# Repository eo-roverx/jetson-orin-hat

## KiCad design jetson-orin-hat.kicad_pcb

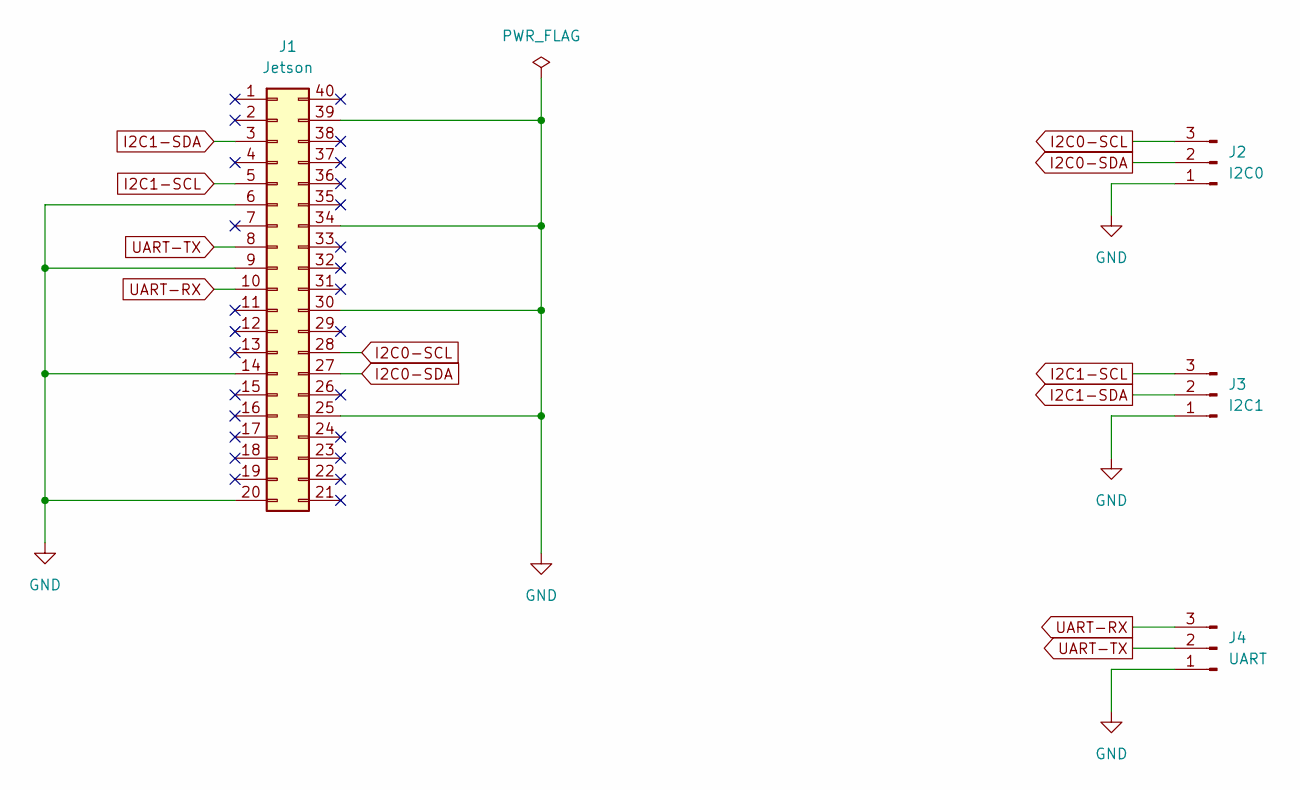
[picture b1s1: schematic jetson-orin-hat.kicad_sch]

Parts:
J1: Jetson; PinHeader_2x20_P2.54mm_Vertical
J2: I2C0; JST_PH_B3B-PH-K_1x03_P2.00mm_Vertical
J3: I2C1; JST_PH_B3B-PH-K_1x03_P2.00mm_Vertical
J4: UART; JST_PH_B3B-PH-K_1x03_P2.00mm_Vertical

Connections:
GND: J1.6, J1.9, J1.14, J1.20, J1.25, J1.30, J1.34, J1.39, J2.1, J3.1, J4.1
I2C0-SCL: J1.28, J2.3
I2C0-SDA: J1.27, J2.2
I2C1-SCL: J1.5, J3.3
I2C1-SDA: J1.3, J3.2
UART-RX: J1.10, J4.3
UART-TX: J1.8, J4.2

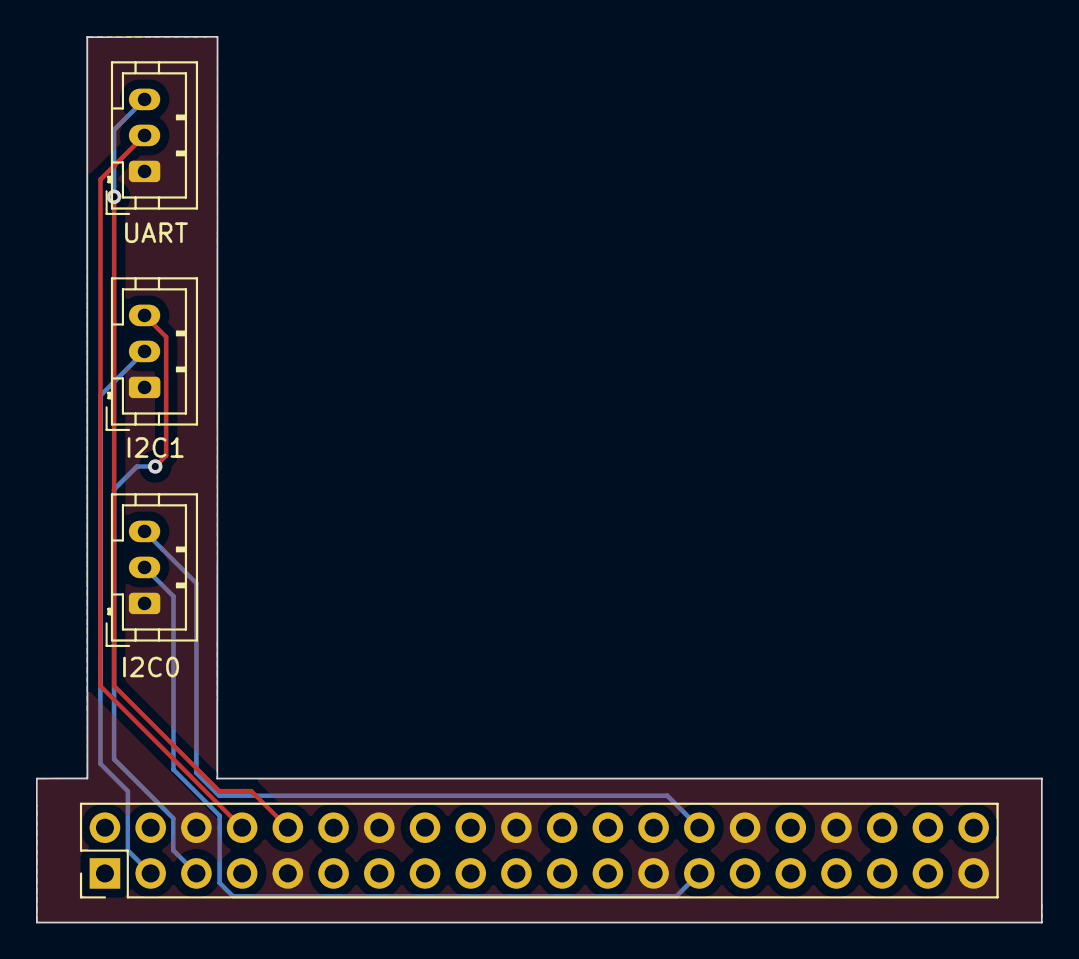
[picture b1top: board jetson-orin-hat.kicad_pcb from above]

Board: 2 copper layers, 55.8 x 49.2 mm, 4 parts (0 on the bottom side), 7 nets.

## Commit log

2023-12-16 first schematic attempt
2023-12-16 done component placement
2023-12-16 done board outline
2023-12-16 edit size
2023-12-16 made fit
2023-12-16 tested with fusion360
